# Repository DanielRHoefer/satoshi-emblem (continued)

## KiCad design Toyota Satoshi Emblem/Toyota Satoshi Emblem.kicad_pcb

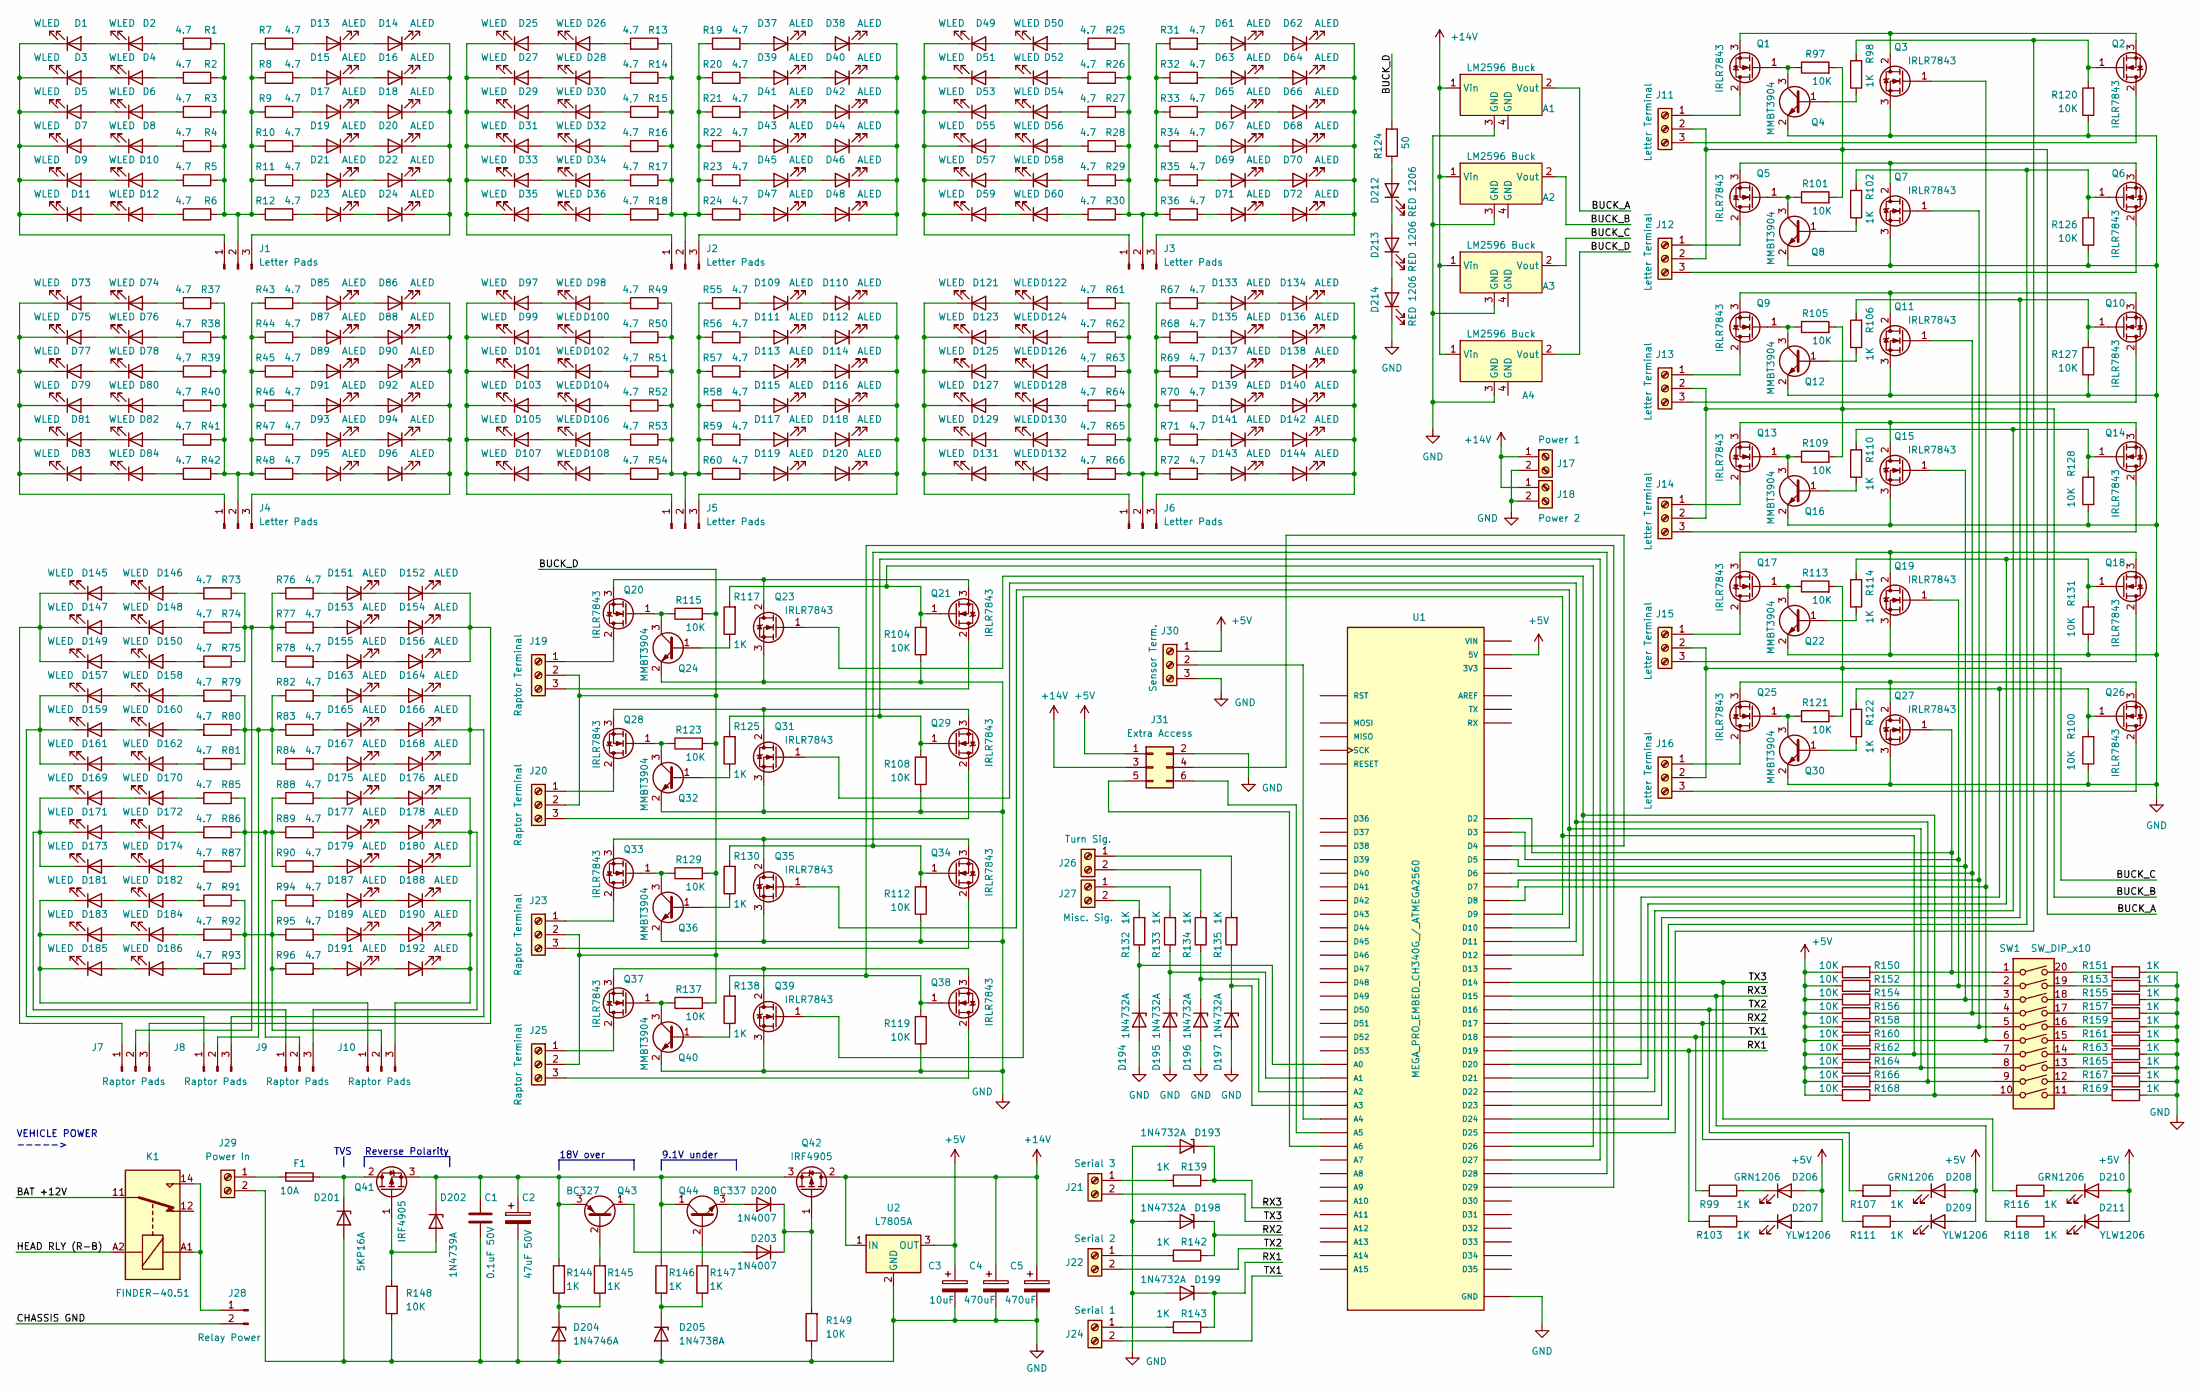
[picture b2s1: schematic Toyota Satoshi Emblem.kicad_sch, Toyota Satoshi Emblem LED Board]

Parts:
A1, A2, A3, A4: LM2596 Buck; LM2596 Buck Converter
C1: 0.1uF 50V; C_Disc_D7.5mm_W5.0mm_P5.00mm
C2: 47uF 50V; C_Radial_D5.0mm_H11.0mm_P2.00mm
C3: 10uF; C_Radial_D4.0mm_H7.0mm_P1.50mm
C4, C5: 470uF; C_Radial_D8.0mm_H11.5mm_P3.50mm
D1, D2, D3, D4, D5, D6, D7, D8, D9, D10, D11, D12, D25, D26, D27, D28, D29, D30, D31, D32, D33, D34, D35, D36, D49, D50, D51, D52, D53, D54, D55, D56, D57, D58, D59, D60, D73, D74, D75, D76, D77, D78, D79, D80, D81, D82, D83, D84, D97, D98, D99, D100, D101, D102, D103, D104, D105, D106, D107, D108, D121, D122, D123, D124, D125, D126, D127, D128, D129, D130, D131, D132, D145, D146, D147, D148, D149, D150, D157, D158, D159, D160, D161, D162, D169, D170, D171, D172, D173, D174, D181, D182, D183, D184, D185, D186: WLED; 5730 LED W
D13, D14, D15, D16, D17, D18, D19, D20, D21, D22, D23, D24, D37, D38, D39, D40, D41, D42, D43, D44, D45, D46, D47, D48, D61, D62, D63, D64, D65, D66, D67, D68, D69, D70, D71, D72, D85, D86, D87, D88, D89, D90, D91, D92, D93, D94, D95, D96, D109, D110, D111, D112, D113, D114, D115, D116, D117, D118, D119, D120, D133, D134, D135, D136, D137, D138, D139, D140, D141, D142, D143, D144, D151, D152, D153, D154, D155, D156, D163, D164, D165, D166, D167, D168, D175, D176, D177, D178, D179, D180, D187, D188, D189, D190, D191, D192: ALED; 5730 LED A
D193, D194, D195, D196, D197, D198, D199: 1N4732A; D_DO-41_SOD81_P10.16mm_Horizontal
D200, D203: 1N4007; D_DO-41_SOD81_P10.16mm_Horizontal
D201: 5KP16A
D202: 1N4739A; D_DO-41_SOD81_P10.16mm_Horizontal
D204: 1N4746A; D_DO-41_SOD81_P10.16mm_Horizontal
D205: 1N4738A; D_DO-41_SOD81_P10.16mm_Horizontal
D206, D208, D210: GRN1206; LED_1206_3216Metric_Pad1.42x1.75mm_HandSolder
D207, D209, D211: YLW1206; LED_1206_3216Metric_Pad1.42x1.75mm_HandSolder
D212, D213, D214: RED 1206; LED_1206_3216Metric_Pad1.42x1.75mm_HandSolder
F1: 10A; Univ_AUTO_Fuse
J1, J2, J3, J4, J5, J6: Letter Pads
J7, J8, J9, J10: Raptor Pads
J11, J12, J13, J14, J15, J16: Letter Terminal; TerminalBlock_Phoenix_MKDS-1,5-3_1x03_P5.00mm_Horizontal
J17: Power 1; TerminalBlock_Phoenix_MKDS-1,5-2_1x02_P5.00mm_Horizontal
J18: Power 2; TerminalBlock_Phoenix_MKDS-1,5-2_1x02_P5.00mm_Horizontal
J19, J20, J23, J25: Raptor Terminal; TerminalBlock_Phoenix_MKDS-1,5-3-5.08_1x03_P5.08mm_Horizont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
J21: Serial 3; TerminalBlock_Phoenix_MKDS-1,5-2_1x02_P5.00mm_Horizontal
J22: Serial 2; TerminalBlock_Phoenix_MKDS-1,5-2_1x02_P5.00mm_Horizontal
J24: Serial 1; TerminalBlock_Phoenix_MKDS-1,5-2_1x02_P5.00mm_Horizontal
J26: Turn Sig.; TerminalBlock_Phoenix_MKDS-1,5-2_1x02_P5.00mm_Horizontal
J27: Misc. Sig.; TerminalBlock_Phoenix_MKDS-1,5-2_1x02_P5.00mm_Horizontal
J28: Relay Power; TerminalBlock_Phoenix_PT-1,5-2-5.0-H_1x02_P5.00mm_Horizontal
J29: Power In; TerminalBlock_Phoenix_MKDS-1,5-2_1x02_P5.00mm_Horizontal
J30: Sensor Term.; TerminalBlock_Phoenix_MKDS-1,5-3_1x03_P5.00mm_Horizontal
J31: Extra Access; PinHeader_2x03_P2.54mm_Vertical
K1: FINDER-40.51; Relay_SPDT_Finder_40.51
Q1, Q2, Q3, Q5, Q6, Q7, Q9, Q10, Q11, Q13, Q14, Q15, Q17, Q18, Q19, Q20, Q21, Q23, Q25, Q26, Q27, Q28, Q29, Q31, Q33, Q34, Q35, Q37, Q38, Q39: IRLR7843
Q4, Q8, Q12, Q16, Q22, Q24, Q30, Q32, Q36, Q40: MMBT3904; SOT-23
Q41, Q42: IRF4905
Q43: BC327; TO-92_Inline
Q44: BC337; TO-92_Inline
R1, R2, R4, R5, R6, R7, R8, R9, R10, R11, R12, R13, R14, R16, R17, R18, R19, R20, R21, R22, R23, R24, R25, R26, R28, R29, R30, R31, R32, R33, R34, R35, R36, R37, R38, R40, R41, R42, R43, R44, R45, R46, R47, R48, R49, R50, R52, R53, R54, R55, R56, R57, R58, R59, R60, R61, R62, R64, R65, R66, R67, R68, R69, R70, R71, R72, R73, R74, R75, R76, R77, R78, R79, R80, R81, R82, R83, R84, R85, R86, R87, R88, R89, R90, R91, R92, R93, R94, R95, R96: 4.7; 1206 R
R3, R15, R27, R39, R51, R63: 4,7; 1206 R
R97, R100, R101, R104, R105, R108, R109, R112, R113, R115, R119, R120, R121, R123, R126, R127, R128, R129, R131, R137, R148, R149, R150, R152, R154, R156, R158, R160, R162, R164, R166, R168: 10K; 1206 R
R98, R99, R102, R103, R106, R107, R110, R111, R114, R116, R117, R118, R122, R125, R130, R132, R133, R134, R135, R138, R139, R142, R143, R144, R145, R146, R147, R151, R153, R155, R157, R159, R161, R163, R165, R167, R169: 1K; 1206 R
R124: 50; 1206 R
SW1: SW_DIP_x10; SW_DIP_SPSTx10_Slide_9.78x27.58mm_W7.62mm_P2.54mm
U1: MEGA_PRO_EMBED_CH340G_/_ATMEGA2560; MODULE_MEGA_PRO_EMBED_CH340G___ATMEGA2560; PARTREV 12/May/2017
U2: L7805A; L7805

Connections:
+5V: C3.1, D206.2 (A), D207.2 (A), D208.2 (A), D209.2 (A), D210.2 (A), D211.2 (A), J30.1, J31.1, R150.1, R152.1, R154.1, R156.1, R158.1, R160.1, R162.1, R164.1, R166.1, R168.1, U1.5V_1 (5V), U1.5V_2 (5V), U1.5V_3 (5V), U2.3 (OUT)
+12V: A1.1 (Vin), A2.1 (Vin), A3.1 (Vin), A4.1 (Vin), C4.1, C5.1, J17.1, J18.1, J31.3, Q42.2 (D), U2.1 (IN)
/BUCK_A: A1.2 (Vout), J11.2, J12.2, R97.2, R101.2
/BUCK_B: A2.2 (Vout), J13.2, J14.2, R105.2, R109.2
/BUCK_C: A3.2 (Vout), J15.2, J16.2, R113.2, R121.2
/BUCK_D: A4.2 (Vout), J19.2, J20.2, J23.2, J25.2, R115.2, R123.2, R124.2, R129.2, R137.2
/RX1: D199.1 (K), R103.2, R143.1, U1.D19
/RX2: D198.1 (K), R111.2, R142.1, U1.D17
/RX3: D193.1 (K), R118.2, R139.1, U1.D15
/TX1: J24.2, R99.2, U1.D18
/TX2: J22.2, R107.2, U1.D16
/TX3: J21.2, R116.2, U1.D14
GND: A1.3 (GND), A2.3 (GND), A3.3 (GND), A4.3 (GND), C1.2, C2.2, C3.2, C4.2, C5.2, D193.2 (A), D194.2 (A), D195.2 (A), D196.2 (A), D197.2 (A), D198.2 (A), D199.2 (A), D201.2 (A2), D204.2 (A), D205.2 (A), D214.1 (K), J17.2, J18.2, J29.2, J30.3, J31.2, Q3.3 (S), Q4.2 (E), Q7.3 (S), Q8.2 (E), Q11.3 (S), Q12.2 (E), Q15.3 (S), Q16.2 (E), Q19.3 (S), Q22.2 (E), Q23.3 (S), Q24.2 (E), Q27.3 (S), Q30.2 (E), Q31.3 (S), Q32.2 (E), Q35.3 (S), Q36.2 (E), Q39.3 (S), Q40.2 (E), R100.1, R104.1, R108.1, R112.1, R119.1, R120.1, R126.1, R127.1, R128.1, R131.1, R148.1, R149.1, R151.1, R153.1, R155.1, R157.1, R159.1, R161.1, R163.1, R165.1, R167.1, R169.1, U1.GND_1 (GND), U1.GND_2 (GND), U1.GND_3 (GND), U2.2 (GND)
unnamed: C1.1, C2.1, D202.1 (K), Q41.3 (S), Q42.3 (S), Q43.3 (E), Q44.1 (C), R144.2, R146.2
unnamed 14: D1.1 (K), D3.1 (K), D5.1 (K), D7.1 (K), D9.1 (K), D11.1 (K), J1.1; also elsewhere on the board
unnamed: D1.2 (A), D2.1 (K)
unnamed: D2.2 (A), R1.2
unnamed: D3.2 (A), D4.1 (K)
unnamed: D4.2 (A), R2.2
unnamed: D5.2 (A), D6.1 (K)
unnamed: D6.2 (A), R3.2
unnamed: D7.2 (A), D8.1 (K)
unnamed: D8.2 (A), R4.2
unnamed: D9.2 (A), D10.1 (K)
unnamed: D10.2 (A), R5.2
unnamed: D11.2 (A), D12.1 (K)
unnamed: D12.2 (A), R6.2
unnamed: D13.1 (K), D14.2 (A)
unnamed: D13.2 (A), R7.2
unnamed 29: D14.1 (K), D16.1 (K), D18.1 (K), D20.1 (K), D22.1 (K), D24.1 (K), J1.3; also elsewhere on the board
unnamed: D15.1 (K), D16.2 (A)
unnamed: D15.2 (A), R8.2
unnamed: D17.1 (K), D18.2 (A)
unnamed: D17.2 (A), R9.2
unnamed: D19.1 (K), D20.2 (A)
unnamed: D19.2 (A), R10.2
unnamed: D21.1 (K), D22.2 (A)
unnamed: D21.2 (A), R11.2
unnamed: D23.1 (K), D24.2 (A)
unnamed: D23.2 (A), R12.2
unnamed 40: D25.1 (K), D27.1 (K), D29.1 (K), D31.1 (K), D33.1 (K), D35.1 (K), J2.1; also elsewhere on the board
unnamed: D25.2 (A), D26.1 (K)
unnamed: D26.2 (A), R13.2
unnamed: D27.2 (A), D28.1 (K)
unnamed: D28.2 (A), R14.2
unnamed: D29.2 (A), D30.1 (K)
unnamed: D30.2 (A), R15.2
unnamed: D31.2 (A), D32.1 (K)
unnamed: D32.2 (A), R16.2
unnamed: D33.2 (A), D34.1 (K)
unnamed: D34.2 (A), R17.2
unnamed: D35.2 (A), D36.1 (K)
unnamed: D36.2 (A), R18.2
unnamed: D37.1 (K), D38.2 (A)
unnamed: D37.2 (A), R19.2
unnamed 55: D38.1 (K), D40.1 (K), D42.1 (K), D44.1 (K), D46.1 (K), D48.1 (K), J2.3; also elsewhere on the board
unnamed: D39.1 (K), D40.2 (A)
unnamed: D39.2 (A), R20.2
unnamed: D41.1 (K), D42.2 (A)
unnamed: D41.2 (A), R21.2
unnamed: D43.1 (K), D44.2 (A)
unnamed: D43.2 (A), R22.2
unnamed: D45.1 (K), D46.2 (A)
unnamed: D45.2 (A), R23.2
unnamed: D47.1 (K), D48.2 (A)
unnamed: D47.2 (A), R24.2
unnamed 66: D49.1 (K), D51.1 (K), D53.1 (K), D55.1 (K), D57.1 (K), D59.1 (K), J3.1; also elsewhere on the board
unnamed: D49.2 (A), D50.1 (K)
unnamed: D50.2 (A), R25.2
unnamed: D51.2 (A), D52.1 (K)
unnamed: D52.2 (A), R26.2
unnamed: D53.2 (A), D54.1 (K)
unnamed: D54.2 (A), R27.2
unnamed: D55.2 (A), D56.1 (K)
unnamed: D56.2 (A), R28.2
unnamed: D57.2 (A), D58.1 (K)
unnamed: D58.2 (A), R29.2
unnamed: D59.2 (A), D60.1 (K)
unnamed: D60.2 (A), R30.2
unnamed: D61.1 (K), D62.2 (A)
unnamed: D61.2 (A), R31.2
unnamed 81: D62.1 (K), D64.1 (K), D66.1 (K), D68.1 (K), D70.1 (K), D72.1 (K), J3.3; also elsewhere on the board
unnamed: D63.1 (K), D64.2 (A)
unnamed: D63.2 (A), R32.2
unnamed: D65.1 (K), D66.2 (A)
unnamed: D65.2 (A), R33.2
unnamed: D67.1 (K), D68.2 (A)
unnamed: D67.2 (A), R34.2
unnamed: D69.1 (K), D70.2 (A)
unnamed: D69.2 (A), R35.2
unnamed: D71.1 (K), D72.2 (A)
unnamed: D71.2 (A), R36.2
unnamed 92: D73.1 (K), D75.1 (K), D77.1 (K), D79.1 (K), D81.1 (K), D83.1 (K), J4.1; also elsewhere on the board
unnamed: D73.2 (A), D74.1 (K)
unnamed: D74.2 (A), R37.2
unnamed: D75.2 (A), D76.1 (K)
unnamed: D76.2 (A), R38.2
unnamed: D77.2 (A), D78.1 (K)
unnamed: D78.2 (A), R39.2
unnamed: D79.2 (A), D80.1 (K)
unnamed: D80.2 (A), R40.2
unnamed: D81.2 (A), D82.1 (K)
unnamed: D82.2 (A), R41.2
unnamed: D83.2 (A), D84.1 (K)
unnamed: D84.2 (A), R42.2
unnamed: D85.1 (K), D86.2 (A)
unnamed: D85.2 (A), R43.2
unnamed 107: D86.1 (K), D88.1 (K), D90.1 (K), D92.1 (K), D94.1 (K), D96.1 (K), J4.3; also elsewhere on the board
unnamed: D87.1 (K), D88.2 (A)
unnamed: D87.2 (A), R44.2
unnamed: D89.1 (K), D90.2 (A)
unnamed: D89.2 (A), R45.2
unnamed: D91.1 (K), D92.2 (A)
unnamed: D91.2 (A), R46.2
unnamed: D93.1 (K), D94.2 (A)
unnamed: D93.2 (A), R47.2
unnamed: D95.1 (K), D96.2 (A)
unnamed: D95.2 (A), R48.2
unnamed: D97.2 (A), D98.1 (K)
unnamed: D98.2 (A), R49.2
unnamed: D99.2 (A), D100.1 (K)
unnamed: D100.2 (A), R50.2
unnamed 122: D97.1 (K), D99.1 (K), D101.1 (K), D103.1 (K), D105.1 (K), D107.1 (K), J5.1; also elsewhere on the board
unnamed: D101.2 (A), D102.1 (K)
unnamed: D102.2 (A), R51.2
unnamed: D103.2 (A), D104.1 (K)
unnamed: D104.2 (A), R52.2
unnamed: D105.2 (A), D106.1 (K)
unnamed: D106.2 (A), R53.2
unnamed: D107.2 (A), D108.1 (K)
unnamed: D108.2 (A), R54.2
unnamed: D109.1 (K), D110.2 (A)
unnamed: D109.2 (A), R55.2
unnamed 133: D110.1 (K), D112.1 (K), D114.1 (K), D116.1 (K), D118.1 (K), D120.1 (K), J5.3; also elsewhere on the board
unnamed: D111.1 (K), D112.2 (A)
unnamed: D111.2 (A), R56.2
unnamed: D113.1 (K), D114.2 (A)
unnamed: D113.2 (A), R57.2
unnamed: D115.1 (K), D116.2 (A)
unnamed: D115.2 (A), R58.2
unnamed: D117.1 (K), D118.2 (A)
unnamed: D117.2 (A), R59.2
unnamed: D119.1 (K), D120.2 (A)
unnamed: D119.2 (A), R60.2
unnamed 144: D121.1 (K), D123.1 (K), D125.1 (K), D127.1 (K), D129.1 (K), D131.1 (K), J6.1; also elsewhere on the board
unnamed: D121.2 (A), D122.1 (K)
unnamed: D122.2 (A), R61.2
unnamed: D123.2 (A), D124.1 (K)
unnamed: D124.2 (A), R62.2
unnamed: D125.2 (A), D126.1 (K)
unnamed: D126.2 (A), R63.2
unnamed: D127.2 (A), D128.1 (K)
unnamed: D128.2 (A), R64.2
unnamed: D129.2 (A), D130.1 (K)
unnamed: D130.2 (A), R65.2
unnamed: D131.2 (A), D132.1 (K)
unnamed: D132.2 (A), R66.2
unnamed: D133.1 (K), D134.2 (A)
unnamed: D133.2 (A), R67.2
unnamed 159: D134.1 (K), D136.1 (K), D138.1 (K), D140.1 (K), D142.1 (K), D144.1 (K), J6.3; also elsewhere on the board
unnamed: D135.1 (K), D136.2 (A)
unnamed: D135.2 (A), R68.2
unnamed: D137.1 (K), D138.2 (A)
unnamed: D137.2 (A), R69.2
unnamed: D139.1 (K), D140.2 (A)
unnamed: D139.2 (A), R70.2
unnamed: D141.1 (K), D142.2 (A)
unnamed: D141.2 (A), R71.2
unnamed: D143.1 (K), D144.2 (A)
unnamed: D143.2 (A), R72.2
unnamed 170: D145.1 (K), D147.1 (K), D149.1 (K), J7.1; also elsewhere on the board
unnamed: D145.2 (A), D146.1 (K)
unnamed: D146.2 (A), R73.2
unnamed: D147.2 (A), D148.1 (K)
unnamed: D148.2 (A), R74.2
unnamed: D149.2 (A), D150.1 (K)
unnamed: D150.2 (A), R75.2
unnamed: D151.1 (K), D152.2 (A)
unnamed: D151.2 (A), R76.2
unnamed 179: D152.1 (K), D154.1 (K), D156.1 (K), J7.3; also elsewhere on the board
unnamed: D153.1 (K), D154.2 (A)
unnamed: D153.2 (A), R77.2
unnamed: D155.1 (K), D156.2 (A)
unnamed: D155.2 (A), R78.2
unnamed 184: D157.1 (K), D159.1 (K), D161.1 (K), J8.1; also elsewhere on the board
unnamed: D157.2 (A), D158.1 (K)
unnamed: D158.2 (A), R79.2
unnamed: D159.2 (A), D160.1 (K)
unnamed: D160.2 (A), R80.2
unnamed: D161.2 (A), D162.1 (K)
unnamed: D162.2 (A), R81.2
unnamed: D163.1 (K), D164.2 (A)
unnamed: D163.2 (A), R82.2
unnamed 193: D164.1 (K), D166.1 (K), D168.1 (K), J8.3; also elsewhere on the board
unnamed: D165.1 (K), D166.2 (A)
unnamed: D165.2 (A), R83.2
unnamed: D167.1 (K), D168.2 (A)
unnamed: D167.2 (A), R84.2
unnamed 198: D169.1 (K), D171.1 (K), D173.1 (K), J9.1; also elsewhere on the board
unnamed: D169.2 (A), D170.1 (K)
unnamed: D170.2 (A), R85.2
unnamed: D171.2 (A), D172.1 (K)
unnamed: D172.2 (A), R86.2
unnamed: D173.2 (A), D174.1 (K)
unnamed: D174.2 (A), R87.2
unnamed: D175.1 (K), D176.2 (A)
unnamed: D175.2 (A), R88.2
unnamed 207: D176.1 (K), D178.1 (K), D180.1 (K), J9.3; also elsewhere on the board
unnamed: D177.1 (K), D178.2 (A)
unnamed: D177.2 (A), R89.2
unnamed: D179.1 (K), D180.2 (A)
unnamed: D179.2 (A), R90.2
unnamed 212: D181.1 (K), D183.1 (K), D185.1 (K), J10.1; also elsewhere on the board
unnamed: D181.2 (A), D182.1 (K)
unnamed: D182.2 (A), R91.2
unnamed: D183.2 (A), D184.1 (K)
unnamed: D184.2 (A), R92.2
unnamed: D185.2 (A), D186.1 (K)
unnamed: D186.2 (A), R93.2
unnamed: D187.1 (K), D188.2 (A)
unnamed: D187.2 (A), R94.2
unnamed 221: D188.1 (K), D190.1 (K), D192.1 (K), J10.3; also elsewhere on the board
unnamed: D189.1 (K), D190.2 (A)
unnamed: D189.2 (A), R95.2
unnamed: D191.1 (K), D192.2 (A)
unnamed: D191.2 (A), R96.2
unnamed: D194.1 (K), R132.1, U1.A0
unnamed: D195.1 (K), R133.1, U1.A1
unnamed: D196.1 (K), R134.1, U1.A2
unnamed: D197.1 (K), R135.1, U1.A3
unnamed: D200.1 (K), D203.1 (K), Q42.1 (G), R149.2
unnamed: D200.2 (A), Q44.3 (E)
unnamed: D201.1 (A1), F1.1, Q41.2 (D)
unnamed: D202.2 (A), Q41.1 (G), R148.2
unnamed: D203.2 (A), Q43.1 (C)
unnamed: D204.1 (K), R144.1, R145.1
unnamed: D205.1 (K), R146.1, R147.1
unnamed: D207.1 (K), R103.1
unnamed: D212.1 (K), D213.2 (A)
unnamed: D212.2 (A), R124.1
unnamed: D213.1 (K), D214.2 (A)
unnamed: F1.2, J29.1
unnamed 242: J1.2, R1.1, R2.1, R3.1, R4.1, R5.1, R6.1, R7.1, R8.1, R9.1, R10.1, R11.1, R12.1; also elsewhere on the board
unnamed 243: J2.2, R13.1, R14.1, R15.1, R16.1, R17.1, R18.1, R19.1, R20.1, R21.1, R22.1, R23.1, R24.1; also elsewhere on the board
unnamed 244: J3.2, R25.1, R26.1, R27.1, R28.1, R29.1, R30.1, R31.1, R32.1, R33.1, R34.1, R35.1, R36.1; also elsewhere on the board
unnamed 245: J4.2, R37.1, R38.1, R39.1, R40.1, R41.1, R42.1, R43.1, R44.1, R45.1, R46.1, R47.1, R48.1; also elsewhere on the board
unnamed 246: J5.2, R49.1, R50.1, R51.1, R52.1, R53.1, R54.1, R55.1, R56.1, R57.1, R58.1, R59.1, R60.1; also elsewhere on the board
unnamed 247: J6.2, R61.1, R62.1, R63.1, R64.1, R65.1, R66.1, R67.1, R68.1, R69.1, R70.1, R71.1, R72.1; also elsewhere on the board
unnamed 248: J7.2, R73.1, R74.1, R75.1, R76.1, R77.1, R78.1; also elsewhere on the board
unnamed 249: J8.2, R79.1, R80.1, R81.1, R82.1, R83.1, R84.1; also elsewhere on the board
unnamed 250: J9.2, R85.1, R86.1, R87.1, R88.1, R89.1, R90.1; also elsewhere on the board
unnamed 251: J10.2, R91.1, R92.1, R93.1, R94.1, R95.1, R96.1; also elsewhere on the board
unnamed: J11.1, Q1.2 (D)
unnamed: J11.3, Q2.2 (D)
unnamed: J12.1, Q5.2 (D)
unnamed: J12.3, Q6.2 (D)
unnamed: J13.1, Q9.2 (D)
unnamed: J13.3, Q10.2 (D)
unnamed: J14.1, Q13.2 (D)
unnamed: J14.3, Q14.2 (D)
unnamed: J15.1, Q17.2 (D)
unnamed: J15.3, Q18.2 (D)
unnamed: J16.1, Q25.2 (D)
unnamed: J16.3, Q26.2 (D)
unnamed: J19.1, Q20.2 (D)
unnamed: J19.3, Q21.2 (D)
unnamed: J20.1, Q28.2 (D)
unnamed: J20.3, Q29.2 (D)
unnamed: J21.1, R139.2
unnamed: J22.1, R142.2
unnamed: J23.1, Q33.2 (D)
unnamed: J23.3, Q34.2 (D)
unnamed: J24.1, R143.2
unnamed: J25.1, Q37.2 (D)
unnamed: J25.3, Q38.2 (D)
unnamed: J26.1, R135.2
unnamed: J26.2, R134.2
unnamed: J27.1, R133.2
unnamed: J27.2, R132.2
unnamed: J28.1, K1.14, K1.A1
unnamed: J30.2, U1.A4
unnamed: Q1.1 (G), Q4.3 (C), R97.1
unnamed: Q1.3 (S), Q2.3 (S), Q3.2 (D)
unnamed: Q2.1 (G), R98.2, R120.2, U1.D25
unnamed: Q3.1 (G), R160.2, SW1.6, U1.D8
unnamed: Q5.1 (G), Q8.3 (C), R101.1
unnamed: Q5.3 (S), Q6.3 (S), Q7.2 (D)
unnamed: Q6.1 (G), R102.2, R126.2, U1.D24
unnamed: Q7.1 (G), R158.2, SW1.5, U1.D7
unnamed: Q9.1 (G), Q12.3 (C), R105.1
unnamed: Q10.1 (G), R106.2, R127.2, U1.D23
unnamed: Q9.3 (S), Q10.3 (S), Q11.2 (D)
unnamed: Q11.1 (G), R156.2, SW1.4, U1.D6
unnamed: Q13.1 (G), Q16.3 (C), R109.1
unnamed: Q13.3 (S), Q14.3 (S), Q15.2 (D)
unnamed: Q14.1 (G), R110.2, R128.2, U1.D22
unnamed: Q15.1 (G), R154.2, SW1.3, U1.D5
unnamed: Q17.1 (G), Q22.3 (C), R113.1
unnamed: Q17.3 (S), Q18.3 (S), Q19.2 (D)
unnamed: Q18.1 (G), R114.2, R131.2, U1.D21
unnamed: Q19.1 (G), R152.2, SW1.2, U1.D3
unnamed: Q20.1 (G), Q24.3 (C), R115.1
unnamed: Q20.3 (S), Q21.3 (S), Q23.2 (D)
unnamed: Q21.1 (G), R104.2, R117.2, U1.D26
unnamed: Q23.1 (G), R168.2, SW1.10, U1.D12
unnamed: Q25.1 (G), Q30.3 (C), R121.1
unnamed: Q25.3 (S), Q26.3 (S), Q27.2 (D)
unnamed: Q26.1 (G), R100.2, R122.2, U1.D20
unnamed: Q27.1 (G), R150.2, SW1.1, U1.D2
unnamed: Q28.1 (G), Q32.3 (C), R123.1
unnamed: Q28.3 (S), Q29.3 (S), Q31.2 (D)
unnamed: Q29.1 (G), R108.2, R125.2, U1.D27
unnamed: Q31.1 (G), R166.2, SW1.9, U1.D11
unnamed: Q33.1 (G), Q36.3 (C), R129.1
unnamed: Q33.3 (S), Q34.3 (S), Q35.2 (D)
unnamed: Q34.1 (G), R112.2, R130.2, U1.D28
unnamed: Q35.1 (G), R164.2, SW1.8, U1.D10
unnamed: Q37.1 (G), Q40.3 (C), R137.1
unnamed: Q37.3 (S), Q38.3 (S), Q39.2 (D)
unnamed: Q38.1 (G), R119.2, R138.2, U1.D29
unnamed: Q39.1 (G), R162.2, SW1.7, U1.D9
unnamed: Q43.2 (B), R145.2
unnamed: Q44.2 (B), R147.2
unnamed: Q4.1 (B), R98.1
unnamed: D206.1 (K), R99.1
unnamed: Q8.1 (B), R102.1
unnamed: Q12.1 (B), R106.1
unnamed: D208.1 (K), R107.1
unnamed: Q16.1 (B), R110.1
unnamed: D209.1 (K), R111.1
unnamed: Q22.1 (B), R114.1
unnamed: D210.1 (K), R116.1
unnamed: Q24.1 (B), R117.1
unnamed: D211.1 (K), R118.1
unnamed: Q30.1 (B), R122.1
unnamed: Q32.1 (B), R125.1
unnamed: Q36.1 (B), R130.1
unnamed: Q40.1 (B), R138.1
unnamed: R151.2, SW1.20
unnamed: R153.2, SW1.19
unnamed: R155.2, SW1.18
unnamed: R157.2, SW1.17
unnamed: R159.2, SW1.16
unnamed: R161.2, SW1.15
unnamed: R163.2, SW1.14
unnamed: R165.2, SW1.13
unnamed: R167.2, SW1.12
unnamed: R169.2, SW1.11
unnamed: U1.3V3_1 (3V3), U1.3V3_2 (3V3)
unnamed: J31.6, U1.A5
unnamed: J31.5, U1.A6
unnamed: J31.4, U1.D4
unnamed: U1.VIN_1 (VIN), U1.VIN_2 (VIN)

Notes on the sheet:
9.1V under
VEHICLE POWER ----->
18V over
Reverse Polarity
TVS

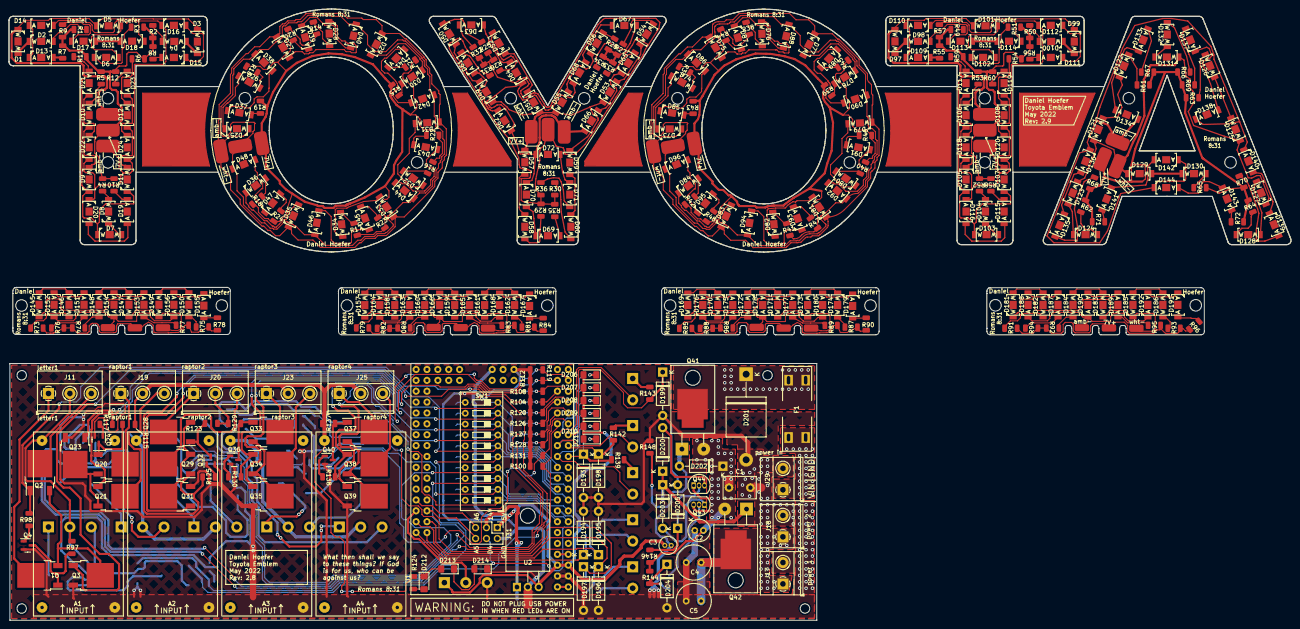
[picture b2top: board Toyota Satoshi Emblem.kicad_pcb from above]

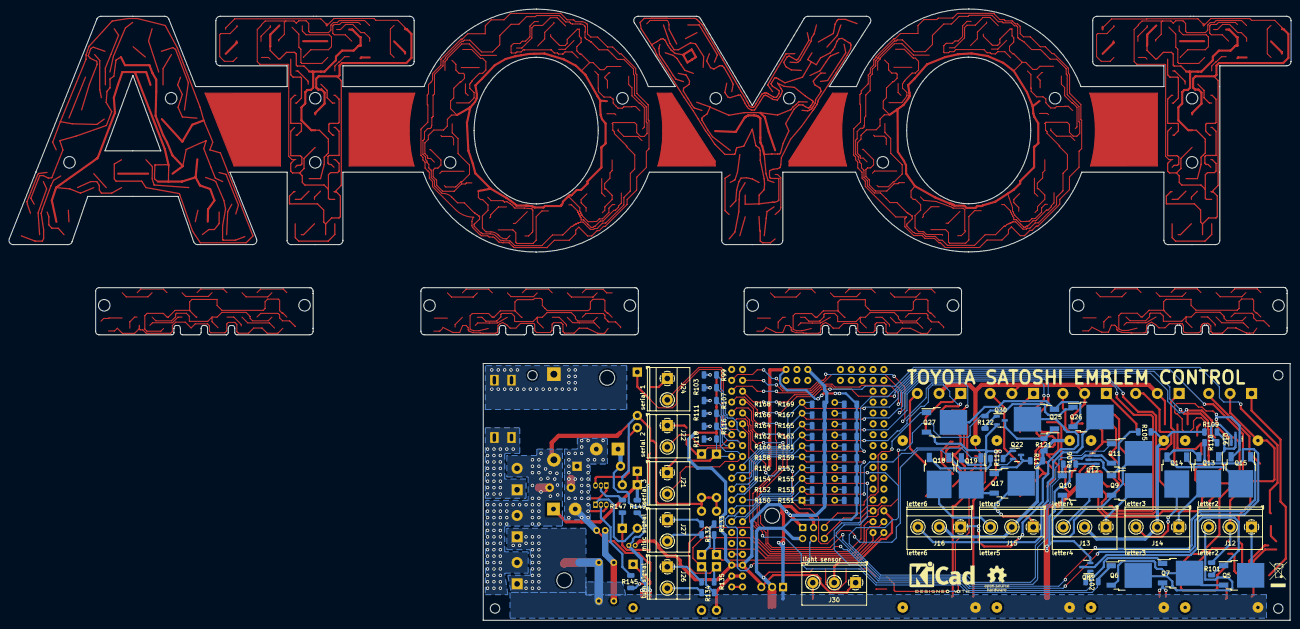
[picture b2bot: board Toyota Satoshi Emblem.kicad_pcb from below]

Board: 2 copper layers, 299.5 x 142.8 mm, 494 parts (77 on the bottom side), 352 nets.

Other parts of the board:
7V+, 7V+#2, 7V+#3, 7V+#4: Pad 2
LOGO1: OSHW-Logo_5.7x6mm_SilkScreen
LOGO2: KiCad-Logo2_6mm_SilkScreen
LOGO3: WEEE-Logo_4.2x6mm_SilkScreen
MT1, MT2, MT3, MT4: MountingHole_2.2mm_M2
P: Pad 1
P#2, P#3, P#4, P#5, P#6, P#7, P#8, P#9, P#10, P#11, P#12, P#13, P#14, P#15, P#16: Pad 1
amb-: Pad 2
amb-#2, amb-#3, amb-#4: Pad 2
wht: Pad 1
wht-: Pad 2
wht-#2, wht-#4, wht-#5: Pad 2
wht-#3: Pad 1

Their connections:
unnamed 14: wht.1; also elsewhere on the board
unnamed 29: P#16.1; also elsewhere on the board
unnamed 40: P#4.1; also elsewhere on the board
unnamed 55: P#8.1; also elsewhere on the board
unnamed 66: P#6.1; also elsewhere on the board
unnamed 81: P#2.1; also elsewhere on the board
unnamed 92: P#9.1; also elsewhere on the board
unnamed 107: P#3.1; also elsewhere on the board
unnamed 122: wht-#3.1; also elsewhere on the board
unnamed 133: P#5.1; also elsewhere on the board
unnamed 144: P#12.1; also elsewhere on the board
unnamed 159: P.1; also elsewhere on the board
unnamed 170: wht-.1; also elsewhere on the board
unnamed 179: amb-#4.1; also elsewhere on the board
unnamed 184: wht-#4.1; also elsewhere on the board
unnamed 193: amb-#2.1; also elsewhere on the board
unnamed 198: wht-#2.1; also elsewhere on the board
unnamed 207: amb-.1; also elsewhere on the board
unnamed 212: wht-#5.1; also elsewhere on the board
unnamed 221: amb-#3.1; also elsewhere on the board
unnamed 242: P#13.1; also elsewhere on the board
unnamed 243: P#15.1; also elsewhere on the board
unnamed 244: P#14.1; also elsewhere on the board
unnamed 245: P#7.1; also elsewhere on the board
unnamed 246: P#10.1; also elsewhere on the board
unnamed 247: P#11.1; also elsewhere on the board
unnamed 248: 7V+.1; also elsewhere on the board
unnamed 249: 7V+#2.1; also elsewhere on the board
unnamed 250: 7V+#4.1; also elsewhere on the board
unnamed 251: 7V+#3.1; also elsewhere on the board

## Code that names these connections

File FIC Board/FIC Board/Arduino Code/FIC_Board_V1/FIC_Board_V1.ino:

#include <Arduino.h>
#include "SiC45x.h"

SiC45x sic45x(0x5C);

#define LET_POWER1 4
#define LET_POWER2 5
#define LET_POWER3 6
#define LET_POWER4 7
#define LET_POWER5 8
#define LET_POWER6 9
#define RAP_POWER1 10
#define RAP_POWER2 11
#define RAP_POWER3 12
#define RAP_POWER4 13

#define LET_COLOR1 22
#define LET_COLOR2 23
#define LET_COLOR3 24
#define LET_COLOR4 25
#define LET_COLOR5 26
#define LET_COLOR6 27
#define RAP_COLOR1 28
#define RAP_COLOR2 29
#define RAP_COLOR3 30
#define RAP_COLOR4 31

#define TURN_P A0
#define TURN_D A1
#define MISC_1 A2
#define MISC_2 A3

int LET_POWER_PIN[6] = {4,5,6,7,8,9};
int RAP_POWER_PIN[4] = {10,11,12,13};
int LET_COLOR_PIN[6] = {22,23,24,25,26,27};
int RAP_COLOR_PIN[4] = {28,29,30,31};

float vout = 6.5; //MAXIMUM OUTPUT VOLTAGE (DO NOT SET ABOVE 7.4V)

boolean c = false;

int state = 0;
boolean action = 0;
byte offAction = 0;

long state_timer = 0;

int animationDelay = 30;

void setup() {
  Serial.begin(115200);   //begin serial communication for debugging

  //wait for a serial connection for debugging
  while(!Serial) {
    delay(10);
  }

  //set all I/O configurations
  for(int i=0; i<6; i++){
    pinMode(LET_POWER_PIN[i], OUTPUT);
    pinMode(LET_COLOR_PIN[i], OUTPUT);
  }
  for(int i=0; i<4; i++){
    pinMode(RAP_POWER_PIN[i], OUTPUT);
    pinMode(RAP_COLOR_PIN[i], OUTPUT);
  }

  pinMode(TURN_D, INPUT); //inputs    
  pinMode(TURN_P, INPUT);
  pinMode(MISC_1, INPUT);
  pinMode(MISC_2, INPUT);

  sic45x.begin();

  sic45x.sendClearFaults();
  sic45x.printStatusWord();

  sic45x.setOperation(
    SIC45X_OPERATION_ON_OFF_DISABLED
    | SIC45X_OPERATION_OFF_B_IMMEDIATE
    | SIC45X_OPERATION_MARGIN_COMMAND
    | SIC45X_OPERATION_MRGNFLT_FOLLOW
  );

  //sic45x.setFrequencySwitch(1000);
  sic45x.setInterleave(SIC45X_INTERLEAVE_MODE_MASTER);

  sic45x.setVoutOvFaultLimit(vout + 1.2);
  sic45x.setVoutOvWarnLimit(vout + 1.1);
  sic45x.setVoutUvWarnLimit(vout - 1.1);
  sic45x.setVoutUvFaultLimit(vout - 1.2);
  sic45x.setVoutUvFaultResponse(
    SIC45X_VOUT_UV_FAULT_RESPONSE_UVRSP_CONTINUE // this basically ignores faults
    | SIC45X_VOUT_UV_FAULT_RESPONSE_UVRTY_NO_RESTART
    | SIC45X_VOUT_UV_FAULT_RESPONSE_UVDLY_NO_DELAY
  );
  sic45x.setVoutScaleLoop(SIC45X_VOUT_SCALE_LOOP_5V0_12V0);
  sic45x.setVoutCommand(vout);
  sic45x.setPowerGoodOn(vout - 0.3);
  sic45x.setPowerGoodOff(vout - 0.6);
  
  sic45x.setVinOvFaultLimit(20);

  sic45x.setOnOffConfiguration(
    SIC45X_ON_OFF_CONFIGURATION_PU_COMMAND
    | SIC45X_ON_OFF_CONFIGURATION_CMD_RESPOND
    | SIC45X_ON_OFF_CONFIGURATION_EN_IGNORE
    | SIC45X_ON_OFF_CONFIGURATION_ENPOL_HIGH
    | SIC45X_ON_OFF_CONFIGURATION_OFFB1_IMMEDIATE
  );

  sic45x.printStatusWord();

  //initial startup states
  for(int i=0; i<6; i++){
    digitalWrite(LET_POWER_PIN[i], LOW);
    digitalWrite(LET_COLOR_PIN[i], LOW);
  }
  for(int i=0; i<4; i++){
    digitalWrite(RAP_POWER_PIN[i], LOW);
    digitalWrite(RAP_COLOR_PIN[i], LOW);
  }

}

void loop() {
    sic45x.setOperation(
      SIC45X_OPERATION_ON_OFF_ENABLED
      | SIC45X_OPERATION_OFF_B_IMMEDIATE
      | SIC45X_OPERATION_MARGIN_COMMAND
      | SIC45X_OPERATION_MRGNFLT_FOLLOW
    );

    if(state != 4 && state != 5) {
      if(digitalRead(TURN_D) == LOW && digitalRead(TURN_P) == LOW) {
        state = 0;    //normal condition
        if(offAction == 1)
          state = 4;
        if(offAction == 2)
          state = 5;
        action = 0;
          
      }
      if(digitalRead(TURN_D) == HIGH && digitalRead(TURN_P) == LOW) {
        state = 1;    //left hand turn
        if(action == 0) {
          state_timer = millis();
          action = 1;
        }
        offAction = 1;
      }
      if(digitalRead(TURN_D) == LOW && digitalRead(TURN_P) == HIGH) {
        state = 2;    //right hand turn
        if(action == 0) {
          state_timer = millis();
          action = 1;
        }
        offAction = 2;
      }
      if(digitalRead(TURN_D) == HIGH && digitalRead(TURN_P) == HIGH) {
        state = 3;    //hazards
        if(action == 0) {
          state_timer = millis();
          action = 1;
        }
      }
    }

    byte allONL[6] = {255,255,255,255,255,255};
    byte allONR[4] = {255,255,255,255};
    byte rapLeft[4] = {255,255,0,0};
    byte rapRight[4] = {0,0,255,255};
    byte allOFFR[4] = {0,0,0,0};
    
    if(state == 0) {
      updateLetters(allONL, B000000);
      updateRaptors(allONR, B0000);

    }
    if(state == 1) {
      updateRaptors(allONR, B1111);
      long stateDuration = millis() - state_timer;

      if(stateDuration < animationDelay*1)
        updateLetters(allONL, B100000);
      else if(stateDuration < animationDelay*2)
        updateLetters(allONL, B110000);
      else if(stateDuration < animationDelay*3)
        updateLetters(allONL, B111000);
      else if(stateDuration < animationDelay*4)
        updateLetters(allONL, B111100);
      else if(stateDuration < animationDelay*5)
        updateLetters(allONL, B111110);
      else if(stateDuration < animationDelay*6)
        updateLetters(allONL, B111111);
    }
    if(state == 2) {

      updateRaptors(allONR, B1111);
      long stateDuration = millis() - state_timer;

      if(stateDuration < animationDelay*1)
        updateLetters(allONL, B000001);
      else if(stateDuration < animationDelay*2)
        updateLetters(allONL, B000011);
      else if(stateDuration < animationDelay*3)
        updateLetters(allONL, B000111);
      else if(stateDuration < animationDelay*4)
        updateLetters(allONL, B001111);
      else if(stateDuration < animationDelay*5)
        updateLetters(allONL, B011111);
      else if(stateDuration < animationDelay*6)
        updateLetters(allONL, B111111);
    }
    if(state == 3) {
      updateLetters(allONL, B111111);
      updateRaptors(allONR, B1111);
    }
    if(state == 4) {
      long stateDuration = millis() - state_timer;
      if(stateDuration > 1500)  {
        offAction = 0;
        state = 0;
      }

      if(digitalRead(TURN_D) == HIGH || digitalRead(TURN_P) == HIGH)  {
        state = 0;
      }
      updateLetters(allONL, B000000);
      updateRaptors(rapRight, B1111);
    }
    if(state == 5) {
      long stateDuration = millis() - state_timer;
      if(stateDuration > 1500)  {
        offAction = 0;
        state = 0;
      }

      if(digitalRead(TURN_D) == HIGH || digitalRead(TURN_P) == HIGH)  {
        state = 0;
      }
      updateLetters(allONL, B000000);
      updateRaptors(rapLeft, B1111);
    }

    Serial.print("state: ");
    Serial.println(state);
    Serial.print("analogVoltage: ");
    Serial.println(analogRead(TURN_D));
    
}

void updateLetters(byte power[6], byte color) {
  for (int i = 0; i < 6; i++) {
    analogWrite(LET_POWER_PIN[i], power[i]);
    digitalWrite(LET_COLOR_PIN[i], !bitRead(color, i));
  }
}

void updateRaptors(byte power[4], byte color) {
  for (int i = 0; i < 4; i++) {
    analogWrite(RAP_POWER_PIN[i], power[i]);
    digitalWrite(RAP_COLOR_PIN[i], !bitRead(color, i));
  }
}

void info() {
   // Report operational parameters every 2s
    Serial.print("IN: V: ");
    Serial.print(sic45x.getReadVin());
    Serial.print("V, I: ");
    Serial.print(sic45x.getReadIin());
    Serial.print("A, P: ");
    Serial.print(sic45x.getReadPin());
    Serial.print("W | OUT: V: ");
    Serial.print(sic45x.getReadVout());
    Serial.print("V, I: ");
    Serial.print(sic45x.getReadIout());
    Serial.print("A, P: ");
    Serial.print(sic45x.getReadPout());
    Serial.print("W | temp: ");
    Serial.print(sic45x.getReadTemperature());
    Serial.print("°C, duty cycle: ");
    Serial.println(sic45x.getReadDutyCycle());
}

void pulse() {
  for(int i=0; i<=255; i++) {
      for(int j=0; j<6; j++) {
        analogWrite(LET_POWER_PIN[j], i);
      }
      for(int j=0; j<4; j++) {
        analogWrite(RAP_POWER_PIN[j], i);
      }
      delay(1); 
    }
    delay(200);
    for(int i=255; i>=0; i--) {
      for(int j=0; j<6; j++) {
        analogWrite(LET_POWER_PIN[j], i);
      }
      for(int j=0; j<4; j++) {
        analogWrite(RAP_POWER_PIN[j], i);
      }
      delayMicroseconds(500); 
    }
    //analogWrite(POWER, 0);
    delay(200);

    
    for(int j=0; j<6; j++) {
      digitalWrite(LET_COLOR_PIN[j], c);
    }
      for(int j=0; j<4; j++) {
      digitalWrite(RAP_COLOR_PIN[j], c);
    }
    c = !c;
}

void on() {
  for(int j=0; j<6; j++) {
      analogWrite(LET_POWER_PIN[j], 255);
      digitalWrite(LET_COLOR_PIN[j], 1);
    }
    for(int j=0; j<4; j++) {
      analogWrite(RAP_POWER_PIN[j], 255);
      digitalWrite(RAP_COLOR_PIN[j], 1);
    }
}

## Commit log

2022-02-19 v1.0
    Initial upload
2022-02-21 v1.1
2022-02-23 v1.2
2022-02-23 v1.3
2022-02-26 v1.4
2022-02-27 v1.5
2022-03-05 v1.6
2022-03-06 v1.7
    More changes to LED pcb. Realized I could link ambers in 3 link series and removing 6 resistors per letter (less heat). Have to redo everything again
2022-03-06 v1.8
    Letter T is now complete
2022-03-10 v1.9
    Letter O and A are now complete
2022-03-16 v1.10
    Second letter O added
2022-03-18 v1.11
    All letters and raptor lights are complete. LED board is nearing completion. Photosensor board is remaining.
2022-04-07 v1.12
    many changes
2022-04-08 v1.13
    Yet more schematic changes
2022-04-09 v1.14
    Control board pcb in the works
2022-04-10 v1.15
    Power sector of PCB mostly completed
2022-04-13 v1.16
    Realized critical errors were made when choosing trace widths. Control PCB will need to be redesigned
2022-04-21 v1.17
    Last push before making some major changes in regards to the processor
2022-04-22 v2.0
    Improved ATmega2560 micro. Future-proofing, but unfortunately have to rebuild the board and led plates yet again.
2022-04-28 v2.1
    probably made some improvements
2022-04-30 v2.2
    Letter T and O are complete
2022-05-01 v2.3
    Letter-board completed w/ silkscreen edits
2022-05-02 v2.4
    Letter-Board and Raptor Lights completed. Onto the Control Board
2022-05-03 v2.5
    Power/control board progress
2022-05-04 v2.6
    More power/control board progress
2022-05-06 v2.7
    More work on the driver circuits
2022-05-07 v2.8
    Finished assembling all boards. Next is final design checking and cleaning things up.
2022-05-12 v2.9
    LED pad polarities and mark will be edited to fix error next rev. Otherwise clearances and board DRC parameters have been refined
2022-05-15 v2.10
    Fixing issues prior to board production
2023-01-30 FIC initial
    major overhaul, new beginnings
2023-02-15 recent updates
2024-02-03 recent
